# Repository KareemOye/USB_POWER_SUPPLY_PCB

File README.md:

# USB Power Supply (12 V to 5 V)

I started this project shortly before beginning my electrical engineering
studies, as a way to learn electronics and circuit design through hands-on
experience. A 12 V to 5 V USB step-down supply seemed like a good first PCB
build, and having now designed and assembled it, I think that was the right
call.

 ## Design

I went with a buck converter rather than a linear regulator, since dropping
12 V to 5 V linearly would waste a very significant amount of power as heat. 
The LM2596S-ADJ handles the switching, and a 1N5822 Schottky diode carries the 
inductor current while the internal switch is off. The feedback pin regulates 
to 1.23 V, so the 3.6 kΩ and 1.2 kΩ divider sets the output to about 4.9 V, 
and a 47 µH inductor smooths the current.

On the input side, a 1.6 A slow-blow fuse protects against shorts and a
470 µF capacitor supplies the pulsed current the converter draws when
switching. At the output, a 330 µF electrolytic and a 100 nF ceramic reduce
ripple, the USB D+ and D- lines are shorted so devices recognise it as a
charger, and a power LED shows when the output is live.

## PCB

The board is a 2-layer approximately 145 × 38 mm design routed in
KiCad, with one SMD component and the rest being through-hole and a ground 
pour on the bottom layer. I kept the input capacitor, LM2596, diode and
inductor close together to keep the high-current switching loop small, which
reduces noise and ringing.

The feedback trace is routed away from the inductor and switching node so
the output regulation isn't disturbed, and the power traces are widened to
1 mm to handle the current. 

## Testing & Measurement

Measured at Vin = 12 V with resistive loads (10.3 Ω, 5.9 Ω, 3.6 Ω), Vout taken at the
USB connector and input power from the bench supply readout. 

Efficiency is about 80 to 83 % up to 0.8 A and drops to about 77 % at 1.36 A, where
the board runs very hot (around 2 W of losses). Vout stays between 4.90 and 4.91 V
from no load to 1.36 A, well inside the USB spec. 

## What I learned

This was my first time taking a circuit all the way from schematic to a
working board. I learned how a buck converter works in practice, how to read
a datasheet to choose supporting components, and how much layout matters
for switching circuits. The build also taught me the practical side:
footprints, ordering parts and hand soldering.

Looking back, the layout is quite spread out and wasn't optimized for size or 
performance. The next revision applies what I learned here, with SMD components, a
tighter layout and a 4-layer stackup, bringing the board down from 145 × 38 mm
to 41 × 37 mm.

## Next revision (in progress)

I am making a second board with the same function but a far more compact 4-layer
design, 41 × 37 mm, built around the TI LMR33630. Unlike the LM2596, it's
a synchronous converter with an integrated low-side switch, so the Schottky
diode is gone and efficiency should improve, especially at higher loads. It
also switches at 400 kHz instead of 150 kHz, which allows a smaller 10 µH
inductor and ceramic output capacitors in place of the large electrolytic.
The divider is now 100 kΩ / 24.9 kΩ against a 1.0 V reference, which would 
make the output 5.02&nbsp;V according to calculation.

The board has already been designed and routed in KiCad, so the remaining
steps are ordering parts, assembly and testing.

Once the second board is assembled and ready I'll compare the two boards on 
efficiency, output ripple and temperature.

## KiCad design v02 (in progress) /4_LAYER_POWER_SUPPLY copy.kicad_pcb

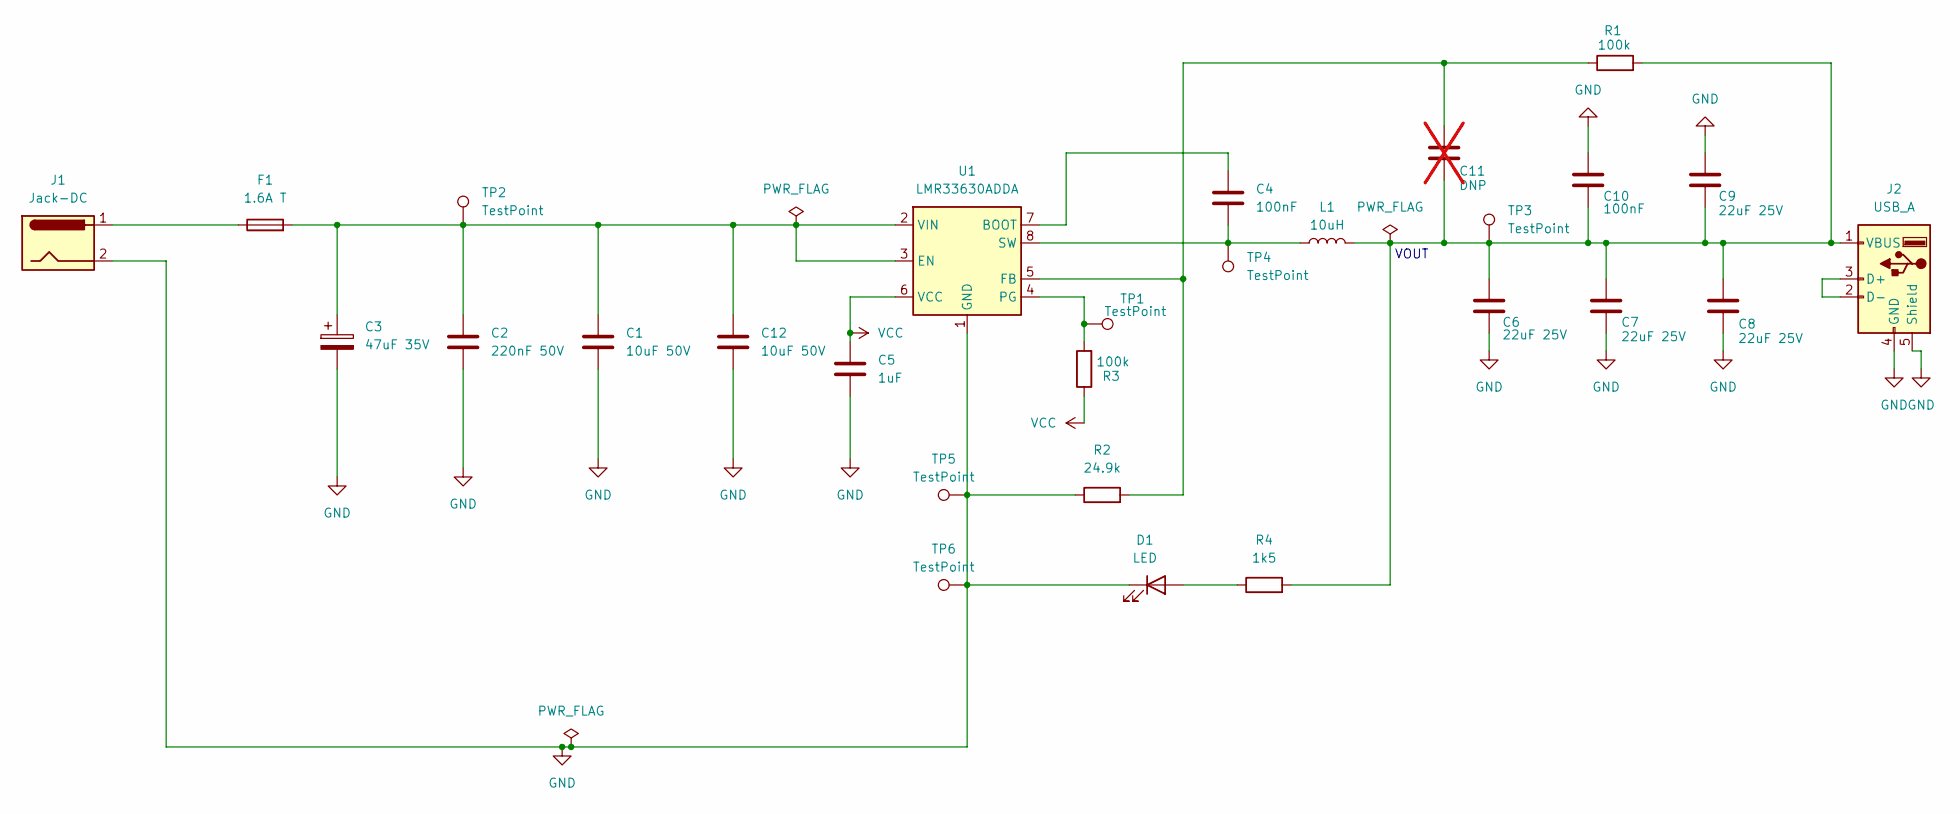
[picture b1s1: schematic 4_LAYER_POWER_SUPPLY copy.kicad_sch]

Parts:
C1, C12: 10uF 50V; C_1210_3225Metric
C2: 220nF 50V; C_0603_1608Metric
C3: 47uF 35V; CP_Elec_6.3x5.8
C4, C10: 100nF; C_0603_1608Metric
C5: 1uF; C_0603_1608Metric
C6, C7, C8, C9: 22uF 25V; C_1210_3225Metric
C11: DNP; C_0603_1608Metric; not fitted
D1: LED; LED_0805_2012Metric
F1: 1.6A T; Fuse_1206_3216Metric
J1: Jack-DC; BarrelJack_CUI_PJ-102AH_Horizontal
J2: USB_A; USB_A_Molex_67643_Horizontal
L1: 10uH; L_Eaton_EXL1V0606
R1, R3: 100k; R_0603_1608Metric
R2: 24.9k; R_0603_1608Metric
R4: 1k5; R_0603_1608Metric
TP1, TP2, TP3, TP4, TP5, TP6: TestPoint; TestPoint_Pad_D1.5mm
U1: LMR33630ADDA; Texas_HSOP-8-1EP_3.9x4.9mm_P1.27mm_ThermalVias

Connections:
GND: C1.2, C2.2, C3.2, C5.2, C6.2, C7.2, C8.2, C9.1, C10.1, C12.2, D1.1 (K), J1.2, J2.4 (GND), J2.5 (Shield), R2.1, TP5.1, TP6.1, U1.1 (GND), U1.9 (GND)
unnamed: D1.2 (A), R4.1
unnamed: F1.1, J1.1
unnamed: J2.2 (D-), J2.3 (D+)
unnamed: C6.1, C7.1, C8.1, C9.2, C10.2, C11.2, J2.1 (VBUS), L1.2, R1.2, R4.2, TP3.1
unnamed: C4.1, U1.7 (BOOT)
unnamed: C1.1, C2.1, C3.1, C12.1, F1.2, TP2.1, U1.2 (VIN), U1.3 (EN)
unnamed: C11.1, R1.1, R2.2, U1.5 (FB)
unnamed: R3.2, TP1.1, U1.4 (PG)
unnamed: C4.2, L1.1, TP4.1, U1.8 (SW)
VCC: C5.1, R3.1, U1.6 (VCC)

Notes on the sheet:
VOUT

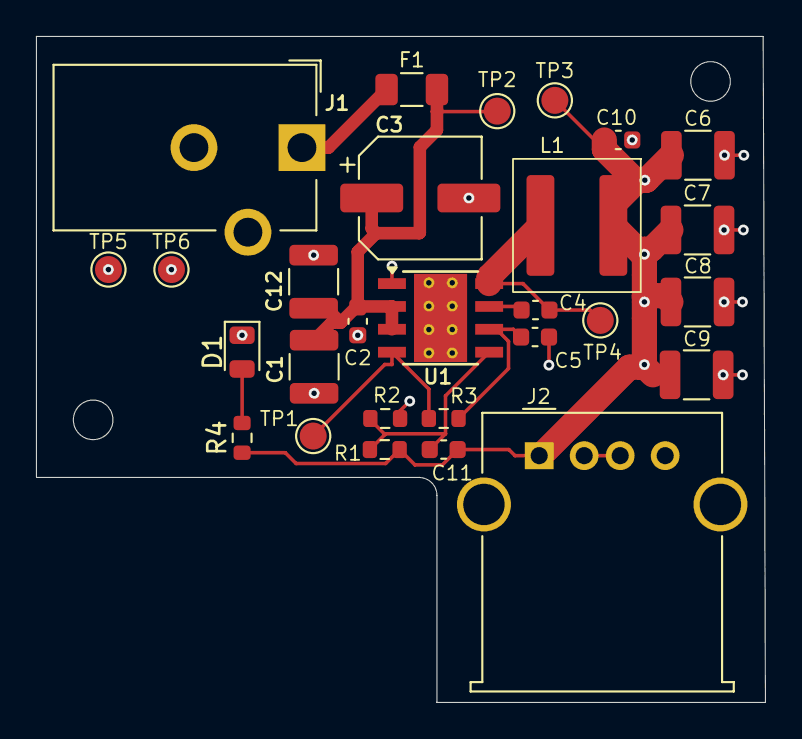
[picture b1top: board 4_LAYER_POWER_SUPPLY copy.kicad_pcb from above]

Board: 4 copper layers, 40.5 x 37.0 mm, 28 parts (0 on the bottom side), 11 nets.

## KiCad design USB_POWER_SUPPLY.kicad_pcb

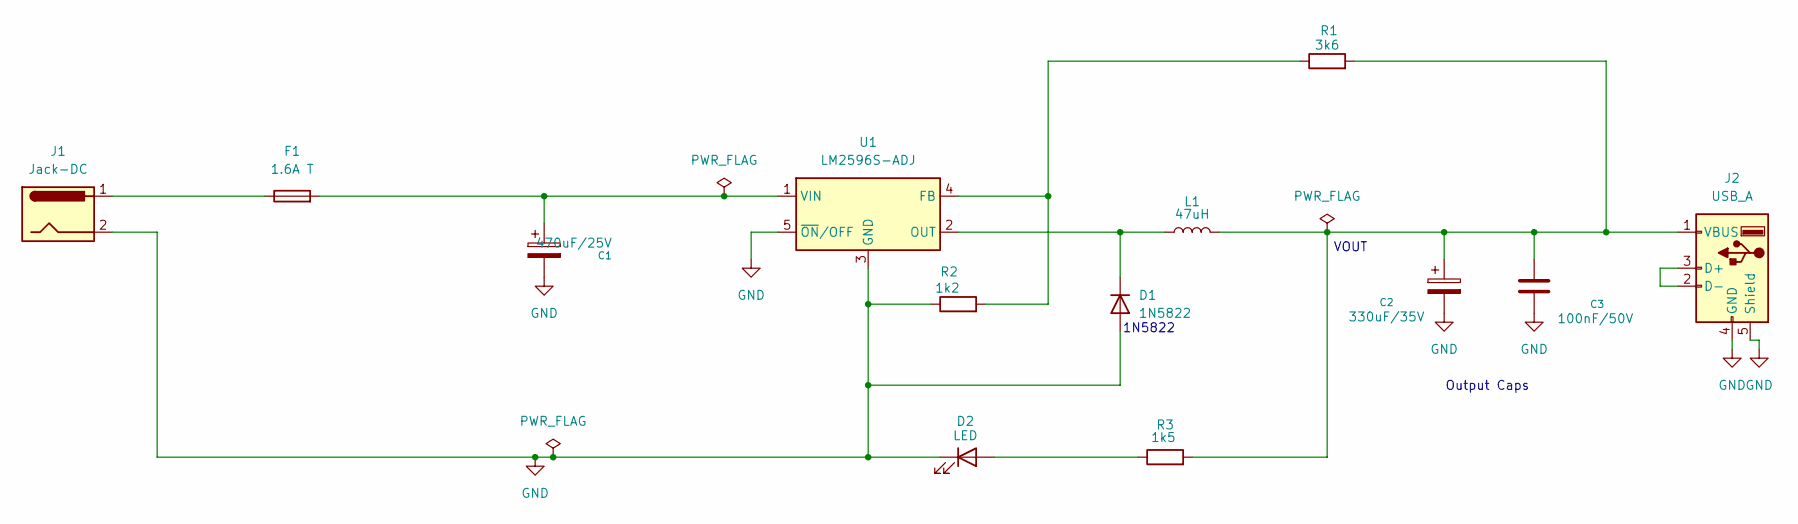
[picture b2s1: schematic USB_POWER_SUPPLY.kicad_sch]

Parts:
C1: 470uF/25V; CP_Radial_D8.0mm_P5.00mm
C2: 330uF/35V; CP_Radial_D10.0mm_P5.00mm
C3: 100nF/50V; C_Disc_D5.0mm_W2.5mm_P5.00mm
D1: 1N5822; D_DO-201AD_P15.24mm_Horizontal
D2: LED; LED_D5.0mm
F1: 1.6A T; Fuseholder_Cylinder-5x20mm_Bulgin_FX0457_Horizontal_Closed
J1: Jack-DC; BarrelJack_CUI_PJ-102AH_Horizontal
J2: USB_A; USB_A_Molex_67643_Horizontal
L1: 47uH; L_Radial_D10.0mm_P5.00mm_Fastron_07P
R1: 3k6; R_Axial_DIN0207_L6.3mm_D2.5mm_P7.62mm_Horizontal
R2: 1k2; R_Axial_DIN0207_L6.3mm_D2.5mm_P7.62mm_Horizontal
R3: 1k5; R_Axial_DIN0207_L6.3mm_D2.5mm_P7.62mm_Horizontal
U1: LM2596S-ADJ; TO-263-5_TabPin3

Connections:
GND: C1.2, C2.2, C3.1, D1.2 (A), D2.1 (K), J1.2, J2.4 (GND), J2.5 (Shield), R2.1, U1.3 (GND), U1.5 (~ON/OFF)
unnamed: D1.1 (K), L1.1, U1.2 (OUT)
unnamed: D2.2 (A), R3.1
unnamed: F1.1, J1.1
unnamed: J2.2 (D-), J2.3 (D+)
unnamed: C2.1, C3.2, J2.1 (VBUS), L1.2, R1.2, R3.2
unnamed: R1.1, R2.2, U1.4 (FB)
unnamed: C1.1, F1.2, U1.1 (VIN)

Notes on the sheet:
VOUT
Output Caps
1N5822

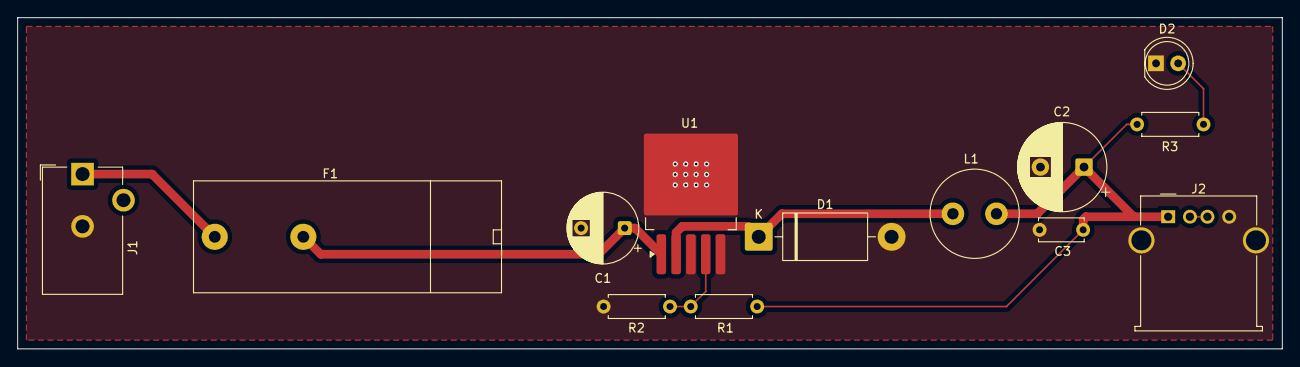
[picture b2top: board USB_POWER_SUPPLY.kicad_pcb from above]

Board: 2 copper layers, 145.1 x 38.0 mm, 13 parts (0 on the bottom side), 8 nets.
